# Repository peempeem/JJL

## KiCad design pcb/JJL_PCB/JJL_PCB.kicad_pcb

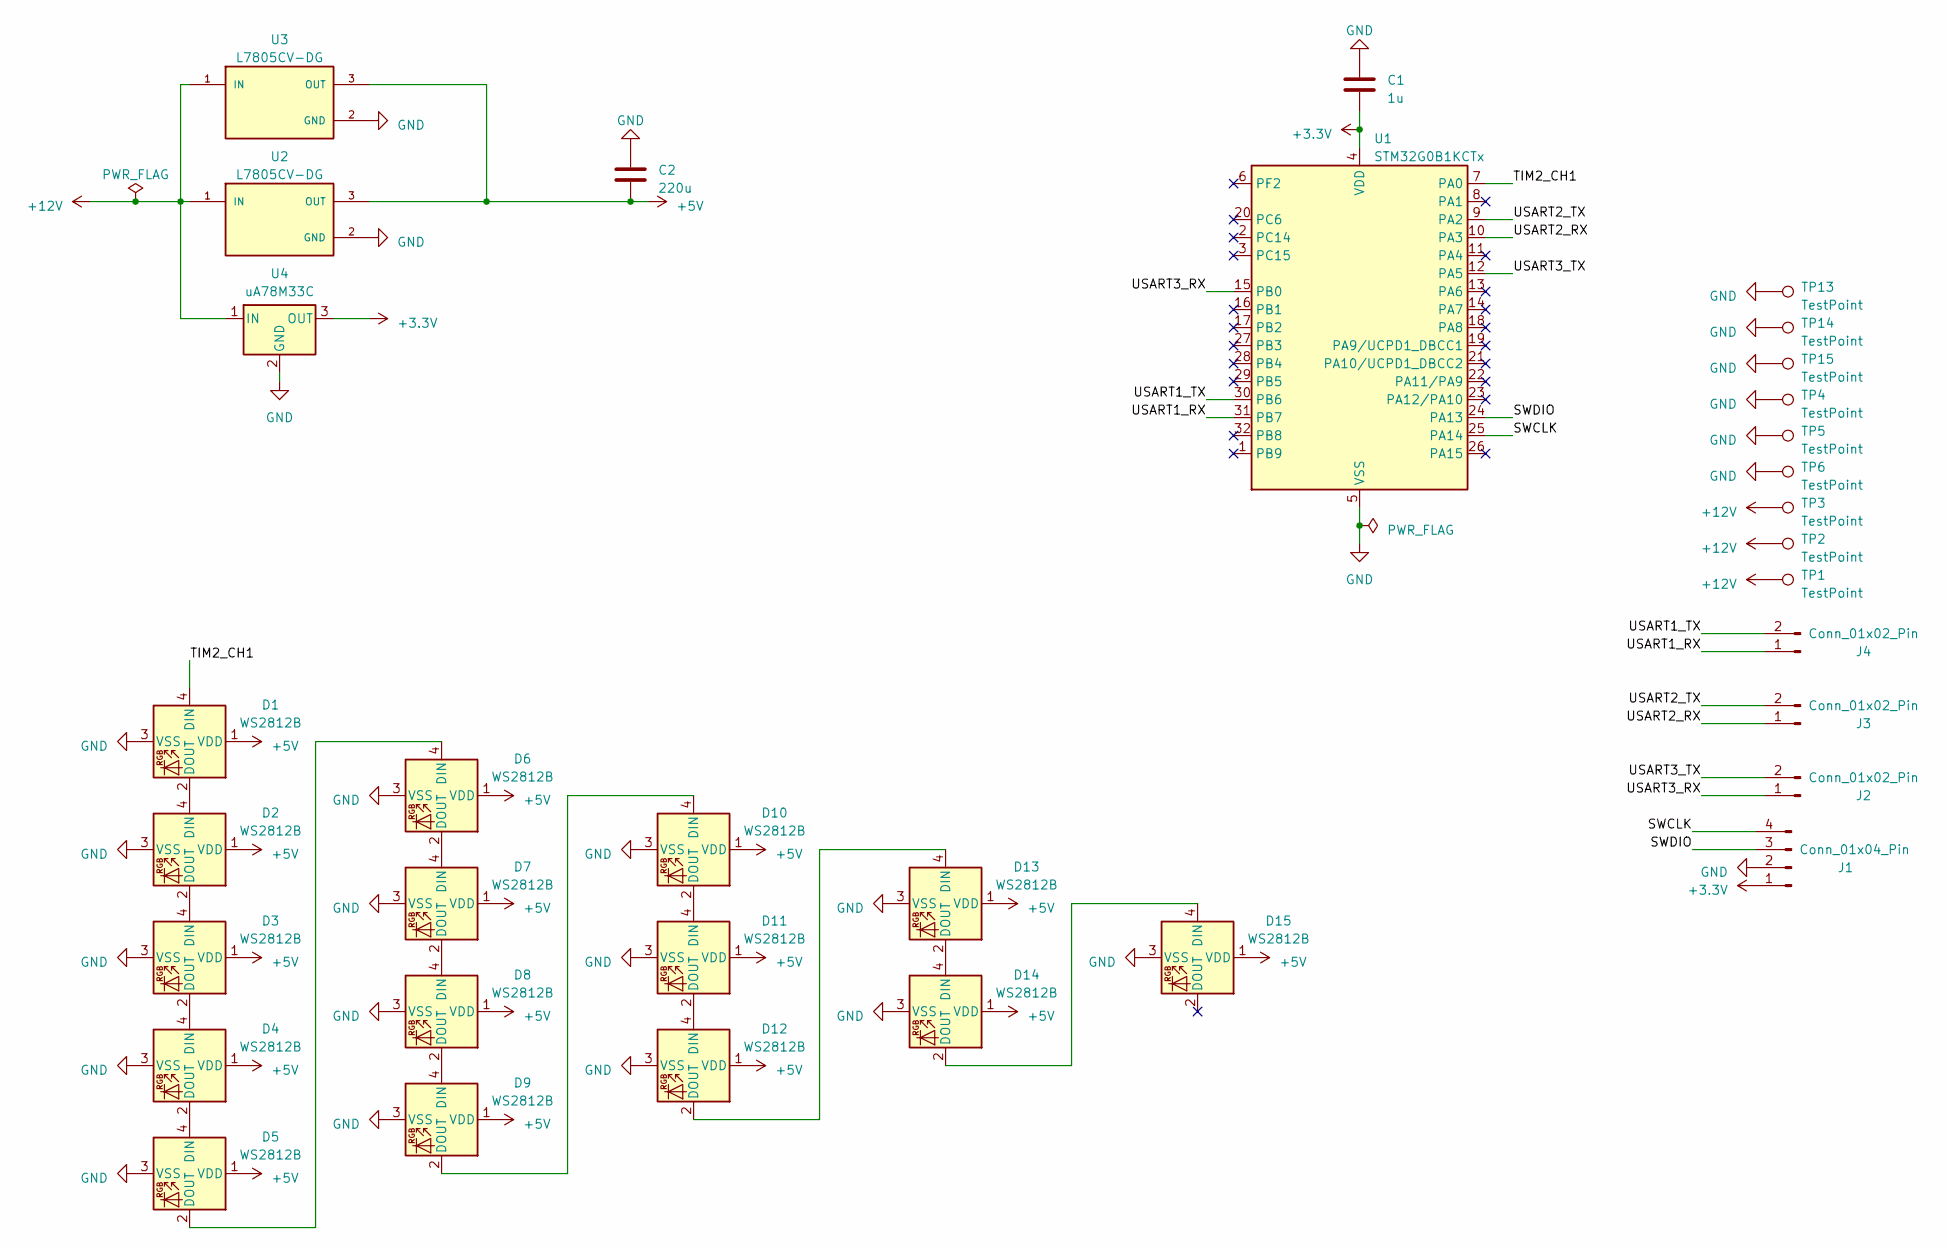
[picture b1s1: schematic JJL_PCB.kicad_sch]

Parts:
C1: 1u; C_0402_1005Metric_Pad0.74x0.62mm_HandSolder
C2: 220u; CP_Radial_D6.3mm_P2.50mm
D1, D2, D3, D4, D5, D6, D7, D8, D9, D10, D11, D12, D13, D14, D15: WS2812B; LED_WS2812B_PLCC4_5.0x5.0mm_P3.2mm
J1: Conn_01x04_Pin; PinHeader_1x04_P2.54mm_Horizontal
J2, J3, J4: Conn_01x02_Pin; PinHeader_1x02_P2.54mm_Vertical
TP1, TP2, TP3: TestPoint; TestPoint_Pad_4.0x4.0mm
TP4, TP5, TP6, TP13, TP14, TP15: TestPoint; TestPoint_Pad_D3.0mm
U1: STM32G0B1KCTx; LQFP-32_7x7mm_P0.8mm
U2, U3: L7805CV-DG; TO255P1040X460X2890-3; PARTREV 36
U4: uA78M33C; TO255P1040X460X2890-3

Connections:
+3.3V: C1.1, J1.1, U1.4 (VDD), U4.3 (OUT)
+5V: C2.2, D1.1 (VDD), D2.1 (VDD), D3.1 (VDD), D4.1 (VDD), D5.1 (VDD), D6.1 (VDD), D7.1 (VDD), D8.1 (VDD), D9.1 (VDD), D10.1 (VDD), D11.1 (VDD), D12.1 (VDD), D13.1 (VDD), D14.1 (VDD), D15.1 (VDD), U2.3 (OUT), U3.3 (OUT)
+12V: TP1.1, TP2.1, TP3.1, U2.1 (IN), U3.1 (IN), U4.1 (IN)
/SWCLK: J1.4, U1.25 (PA14)
/SWDIO: J1.3, U1.24 (PA13)
/TIM2_CH1: D1.4 (DIN), U1.7 (PA0)
/USART1_RX: J4.1, U1.31 (PB7)
/USART1_TX: J4.2, U1.30 (PB6)
/USART2_RX: J3.1, U1.10 (PA3)
/USART2_TX: J3.2, U1.9 (PA2)
/USART3_RX: J2.1, U1.15 (PB0)
/USART3_TX: J2.2, U1.12 (PA5)
GND: C1.2, C2.1, D1.3 (VSS), D2.3 (VSS), D3.3 (VSS), D4.3 (VSS), D5.3 (VSS), D6.3 (VSS), D7.3 (VSS), D8.3 (VSS), D9.3 (VSS), D10.3 (VSS), D11.3 (VSS), D12.3 (VSS), D13.3 (VSS), D14.3 (VSS), D15.3 (VSS), J1.2, TP4.1, TP5.1, TP6.1, TP13.1, TP14.1, TP15.1, U1.5 (VSS), U2.2 (GND), U3.2 (GND), U4.2 (GND)
unnamed: D1.2 (DOUT), D2.4 (DIN)
unnamed: D2.2 (DOUT), D3.4 (DIN)
unnamed: D3.2 (DOUT), D4.4 (DIN)
unnamed: D4.2 (DOUT), D5.4 (DIN)
unnamed: D5.2 (DOUT), D6.4 (DIN)
unnamed: D6.2 (DOUT), D7.4 (DIN)
unnamed: D7.2 (DOUT), D8.4 (DIN)
unnamed: D8.2 (DOUT), D9.4 (DIN)
unnamed: D9.2 (DOUT), D10.4 (DIN)
unnamed: D10.2 (DOUT), D11.4 (DIN)
unnamed: D11.2 (DOUT), D12.4 (DIN)
unnamed: D12.2 (DOUT), D13.4 (DIN)
unnamed: D13.2 (DOUT), D14.4 (DIN)
unnamed: D14.2 (DOUT), D15.4 (DIN)

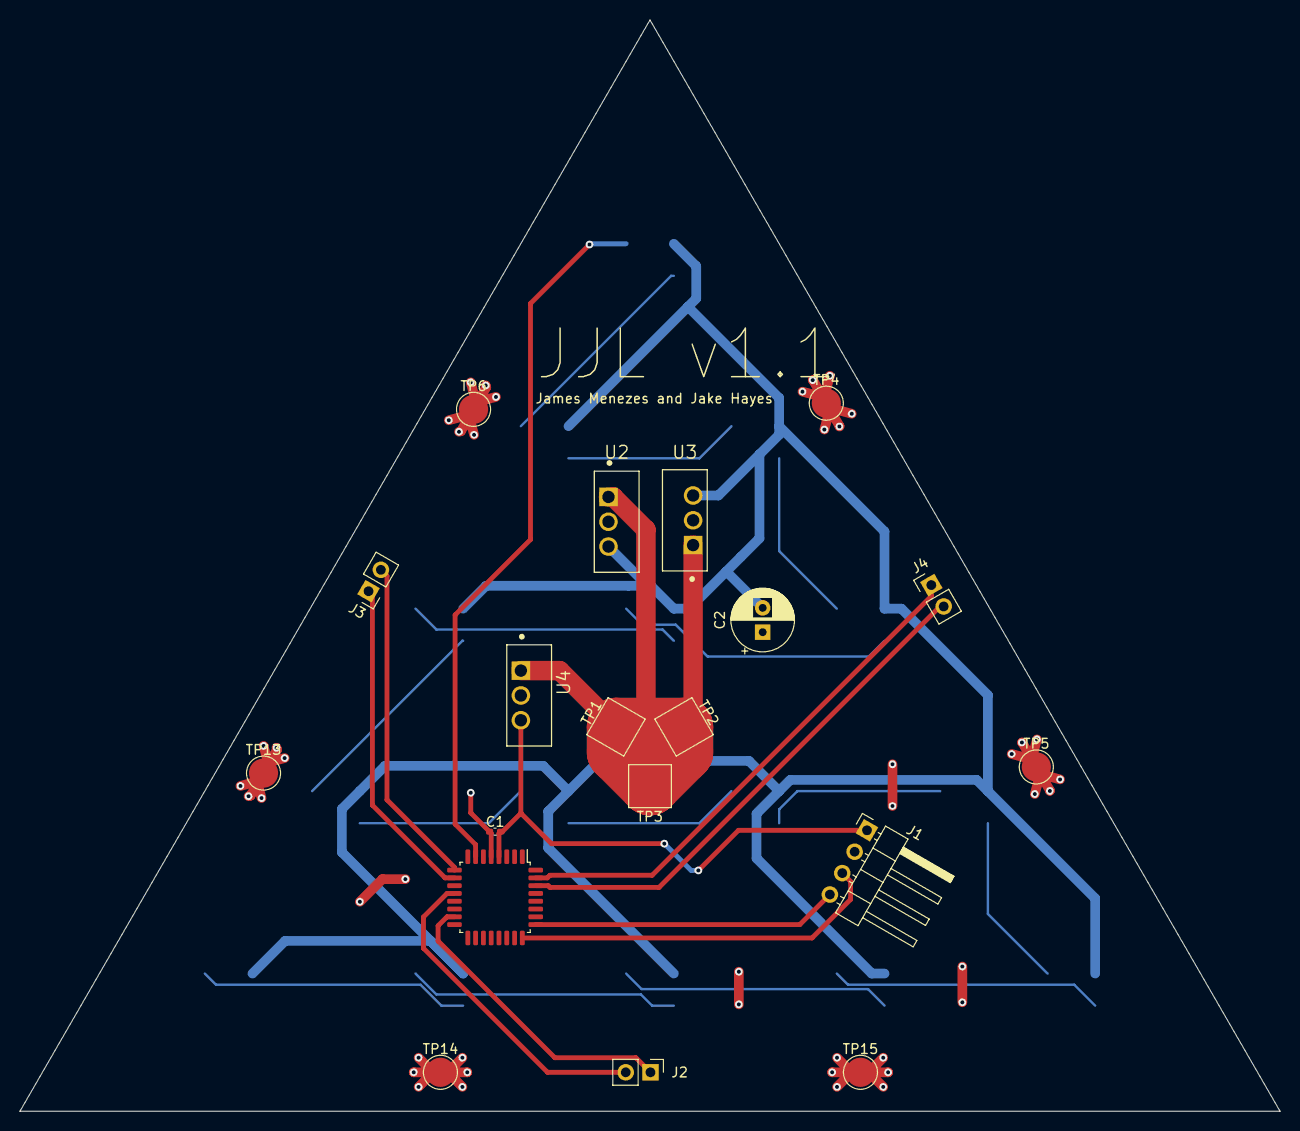
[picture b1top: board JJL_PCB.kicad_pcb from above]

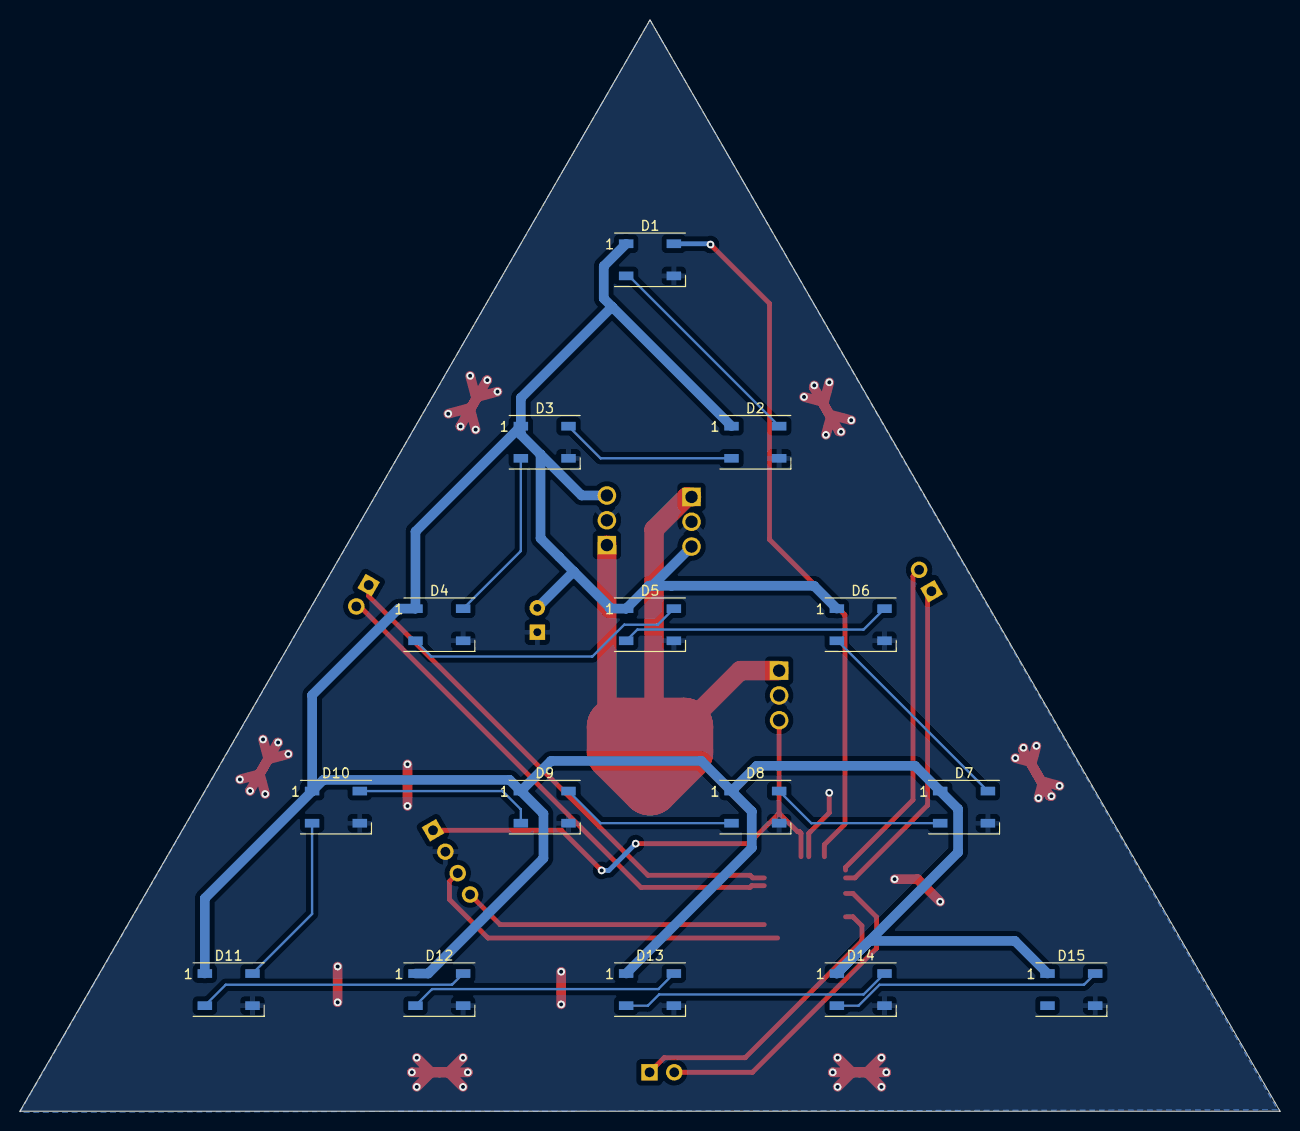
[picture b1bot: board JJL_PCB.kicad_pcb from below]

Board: 2 copper layers, 129.5 x 112.2 mm, 34 parts (15 on the bottom side), 27 nets.

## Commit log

2023-02-18 added comm
2023-02-19 working on the mesh
2023-02-20 working on message hub logic
2023-02-21 progress moment pog
2023-02-24 grapH!!!
2023-02-28 alotta progress pogu
2023-03-01 working on stm32 bugs
2023-03-06 poggers
2023-03-21 fixed comm bugs, uart runs at 1Mb/s
2023-03-31 latest
2023-05-10 final
